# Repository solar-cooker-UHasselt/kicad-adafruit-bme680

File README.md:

# kicad-adafruit-bme680

A breakout board for the Bosch BME680, an environmental sensor that measures
temperature, humidity, barometric pressure and VOC gas, with a 3.3 V regulator and
level shifting so it works with 3.3 V and 5 V boards. It is a KiCad 10 port of
[Adafruit's BME680 breakout](https://github.com/adafruit/Adafruit-BME680-PCB),
originally drawn in Eagle.

In the [solar cooker](https://github.com/solar-cooker-UHasselt) testing station, the
firmware ([arduino-code](https://github.com/solar-cooker-UHasselt/arduino-code)) reads
the ambient temperature, humidity and pressure from it over SPI.

- [Board page](https://solar-cooker-uhasselt.github.io/kicad-adafruit-bme680/): 3D
  renders, drawings, schematic and board PDF, interactive BOM and the BOM CSV for
  Eurocircuits, rebuilt by CI on every push to `main`
- [PCB source](https://github.com/adafruit/Adafruit-BME680-PCB): Adafruit's Eagle files
- [Adafruit guide](https://learn.adafruit.com/adafruit-bme680-humidity-temperature-barometic-pressure-voc-gas):
  pinout, wiring and Arduino examples

## Installation

### Requirements

- [KiCad 10](https://www.kicad.org/download/), to open and edit the board
- [git](https://git-scm.com), to clone the repo with its library
- Optional, for the checks: [just](https://just.systems)

### Clone

Own footprints come from
[kicad-common](https://github.com/solar-cooker-UHasselt/kicad-common), a git submodule
at `kicad-common/`. Clone with it:

```bash
git clone --recurse-submodules https://github.com/solar-cooker-UHasselt/kicad-adafruit-bme680.git
```

Or, in a clone made without it:

```bash
git submodule update --init
```

## Usage

Open `BME680.kicad_pro` in KiCad 10. The schematic and board open from there.

Before committing, run ERC and DRC, reports in `tmp/`:

```bash
just check
```

`just --list` shows the other recipes: PDFs, and the CI workflow run locally.

## Contributing

Branches, pull requests, approval and commits work as in every repo of the org, see
[CONTRIBUTING.md](https://github.com/solar-cooker-UHasselt/.github/blob/main/.github/CONTRIBUTING.md).
Specific to this repo:

- CI runs ERC and DRC on every pull request, through the shared workflows in
  [kicad-ci](https://github.com/solar-cooker-UHasselt/kicad-ci). A push to `main` that
  changes more than Markdown also rebuilds the board page.
- Types, scopes and the ERC/DRC check for commits are in
  [.agents/commit_conventions.md](.agents/commit_conventions.md).
- Changes to the board setup, CI or docs are made and tested in
  [kicad-adafruit-ds3231](https://github.com/solar-cooker-UHasselt/kicad-adafruit-ds3231)
  first, then copied here.

## Authors and acknowledgment

The board is Adafruit's design, by Limor Fried/Ladyada for Adafruit Industries
([PCB source](https://github.com/adafruit/Adafruit-BME680-PCB)). The KiCad 10 port is by
Lowie Van Vyve for the UHasselt solar cooker project.

Adafruit invests time and resources providing this open source design. Please support
Adafruit and open-source hardware by purchasing products from
[Adafruit](https://www.adafruit.com).

<details>
<summary>Adafruit's original README, included as its license asks</summary>

> **Adafruit BME680 PCB**
>
> [Click here to purchase one from the Adafruit shop](http://www.adafruit.com/products/3660)
>
> PCB files for the Adafruit BME680 Breakout. Format is EagleCAD schematic and board
> layout
>
> For more details, check out the product page at
>
> - https://www.adafruit.com/product/3660
>
> **Description**
>
> The long awaited BME680 from Bosch gives you all the environmental sensing you want in
> one small package. This little sensor contains temperature, humidity, barometric
> pressure, and VOC gas sensing capabilities. All over SPI or I2C at a great price!
>
> Like the BME280 & BMP280, this precision sensor from Bosch can measure humidity with
> ±3% accuracy, barometric pressure with ±1 hPa absolute accuracy, and temperature with
> ±1.0°C accuracy. Because pressure changes with altitude, and the pressure measurements
> are so good, you can also use it as an altimeter with ±1 meter or better accuracy!
>
> The BME680 takes those sensors to the next step in that it contains a small MOX
> sensor. The heated metal oxide changes resistance based on the volatile organic
> compounds (VOC) in the air, so it can be used to detect gasses & alcohols such as
> Ethanol, Alcohol and Carbon Monoxide, and perform air quality measurements. Note it
> will give you one resistance value, with overall VOC content, but it cannot
> differentiate gasses or alcohols.
>
> Please note this sensor, like all VOC/gas sensors, has variability and to get precise
> measurements you will want to calibrate it against known sources! That said, for
> general environmental sensors, it will give you a good idea of trends and comparisons.
> We recommend that you run this sensor for 48 hours when you first receive it to "burn
> it in", and then 30 minutes in the desired mode every time the sensor is in use. This
> is because the sensitivity levels of the sensor will change during early use, and the
> resistance will slowly rise over time as the MOX warms up to its baseline reading.
>
> For your convenience we've pick-and-placed the sensor on a PCB with a 3.3V regulator
> and some level shifting, so it can be easily used with your favorite 3.3V or 5V
> microcontroller.
>
> **License**
>
> Adafruit invests time and resources providing this open source design, please support
> Adafruit and open-source hardware by purchasing products from
> [Adafruit](https://www.adafruit.com)!
>
> Designed by Limor Fried/Ladyada for Adafruit Industries.
>
> Creative Commons Attribution/Share-Alike, all text above must be included in any
> redistribution. See license.txt for additional details.

</details>

## License

[CC BY-SA 4.0](LICENSE). Adafruit's original design is licensed CC BY-SA 3.0, which
allows adaptations like this port under a later version with the same terms.

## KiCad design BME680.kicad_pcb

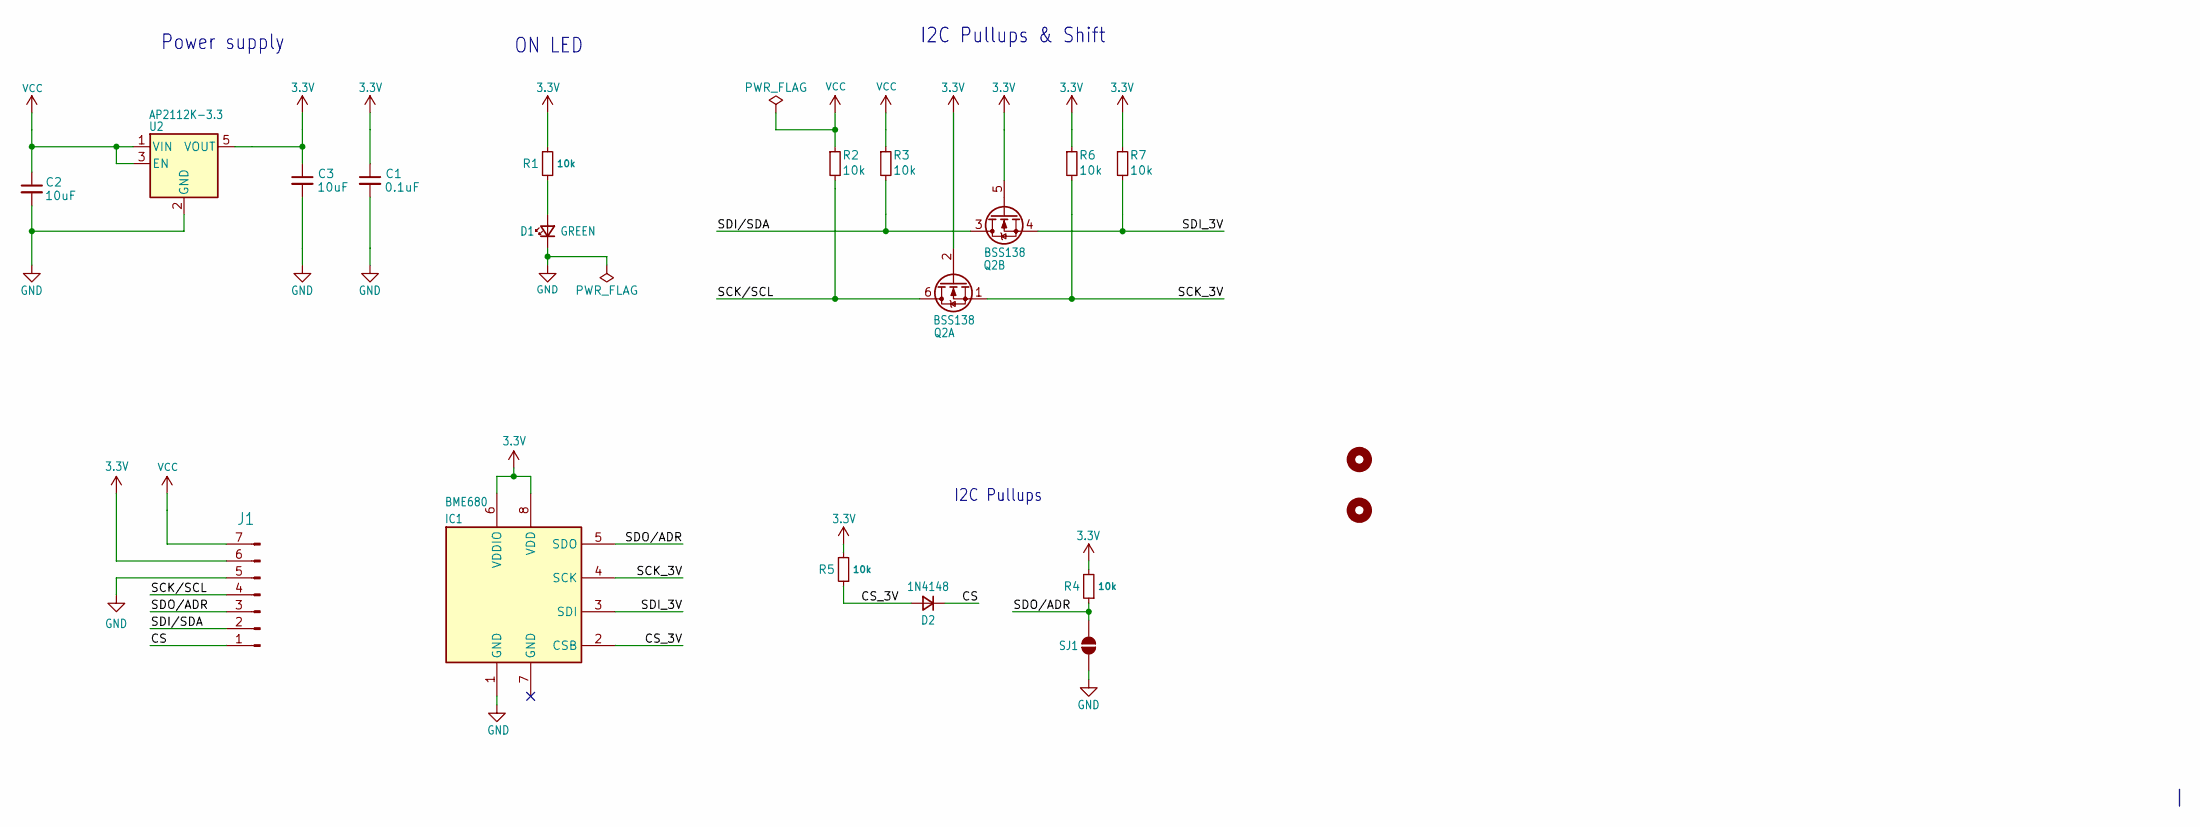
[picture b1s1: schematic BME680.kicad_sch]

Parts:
C1: 0.1uF; C_0603_1608Metric; MPN /
C2, C3: 10uF; C_0805_2012Metric; MPN /
D1: GREEN; LED_0603_1608Metric; MPN 150060GS75000
D2: 1N4148; D_SOD-323; MPN 1N4148WX-TP
IC1: BME680; Bosch_LGA-8_3x3mm_P0.8mm_ClockwisePinNumbering; MPN BME680
J1: HEADER-1X770MIL; PinHeader_1x07_P2.54mm_Vertical; MPN TSW-107-23-G-S
Q2: BSS138; SOT-363_SC-70-6; MPN BSS138DWQ-7
R1, R2, R3, R4, R5, R6, R7: 10k; R_0603_1608Metric; MPN /
SJ1: SOLDERJUMPER; SolderJumper-2_P1.3mm_Open_TrianglePad1.0x1.5mm
U2: AP2112K-3.3; SOT-23-5; MPN AP2112K-3.3TRG1
U$1, U$17: MOUNTINGHOLE2.5; MountingHole_2.5mm

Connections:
3.3V: C1.1, C3.1, IC1.6 (VDDIO), IC1.8 (VDD), J1.6, Q2.2 (G), Q2.5 (G), R1.1, R4.2, R5.2, R6.1, R7.1, U2.5 (VOUT)
/CS: D2.1 (K), J1.1
/CS_3V: D2.2 (A), IC1.2 (CSB), R5.1
/SCK_3V: IC1.4 (SCK), Q2.1 (S), R6.2
/SCK/SCL: J1.4, Q2.6 (D), R2.2
/SDI_3V: IC1.3 (SDI), Q2.4 (S), R7.2
/SDI/SDA: J1.2, Q2.3 (D), R3.2
/SDO/ADR: IC1.5 (SDO), J1.3, R4.1, SJ1.1 (A)
GND: C1.2, C2.2, C3.2, D1.1 (K), IC1.1 (GND), J1.5, SJ1.2 (B), U2.2 (GND)
unnamed: D1.2 (A), R1.2
VCC: C2.1, J1.7, R2.1, R3.1, U2.1 (VIN), U2.3 (EN)

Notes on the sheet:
I2C Pullups
I2C Pullups & Shift
Power supply
ON LED

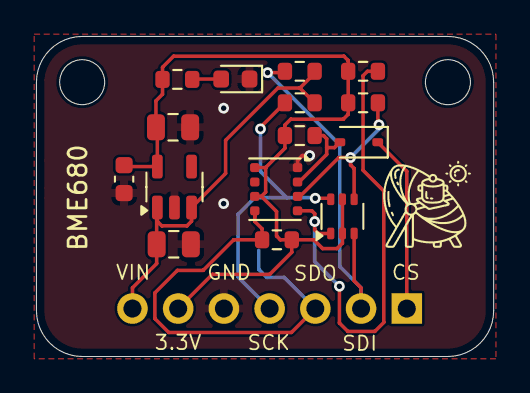
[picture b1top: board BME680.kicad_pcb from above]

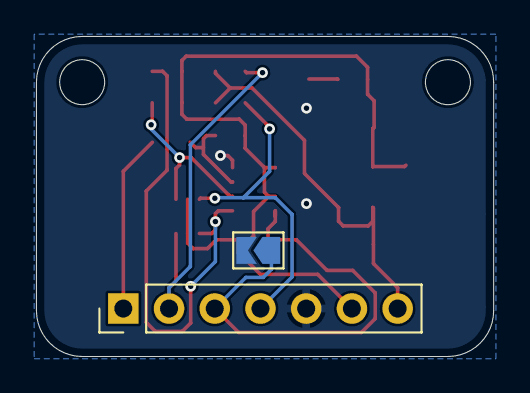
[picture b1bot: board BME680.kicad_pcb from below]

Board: 2 copper layers, 25.4 x 17.8 mm, 19 parts (2 on the bottom side), 11 nets.

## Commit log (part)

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2024-03-05 .gitignore update
2024-03-05 blank KiCad project
2024-03-05 Eagle import
2024-03-06 added drawing sheet
2024-03-13 updated all 3.3v libraries
2024-03-13 updated all ground libraries
2024-03-13 updated all vcc libraries
2024-03-13 updated all resistor libraries
2024-03-13 updated all capacitor libraries
2024-03-13 updated all diode libraries
2024-03-13 updated all solder jumper libraries
2024-03-13 fixed mistake on resistors
2024-03-13 updated nmos libraty
2024-03-14 fixed path issue
2024-03-27 update BME680 scheme
2024-03-28 update BME680 routing and footprints
2024-03-28 minor fixes in silkscreen and schematic layout
2024-04-01 routing done with freerouting + delete stemma connectors
2024-04-01 connector 3D model update
2024-04-01 silkscreen update + BOM finalisation
2024-04-01 BOM update
2024-04-01 production ready
2024-04-03 connector out of stock
2024-04-03 changed copper finish + solder mask and silkscreen color update
2024-04-04 KiBot DRC check workflow
2024-04-05 connector out of stock update
2024-05-02 update README.md + changed pin header orientation
2024-05-17 mosfet update
2024-05-17 removed Eagle import library
2024-05-17 DRC fix
2024-05-21 solder jumper fix
2024-06-10 BOM presets update
